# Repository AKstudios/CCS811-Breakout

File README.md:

# CCS811 Breakout
This is a breakout board for the <a href="http://www.ccmoss.com/gas-sensors#CCS811">CCS811</a>(VOC/eCO2) gas sensor by <a href="http://ams.com/eng/Products/Environmental-Sensors/Gas-Sensors/CCS811">AMS</a>. All necessary pins for interfacing with the sensor are broken out. There is no external temperature and relative humidity sensor on the breakout and hence, the AUX pin is left floating. Temperature and relative humidity data from an external sensor can be manually written to ENV_DATA register (0x05) for dynamic compensation. Optionally, you can add 10K-ohm pull-ups on SDA and SCL when using with other devices on the bus.

Note: After reflow, allow 24-48 hours of burn-in time before the sensor starts reporting any good readings.

Arduino library available <a href="https://github.com/AKstudios/CCS811-library">here</a>.

<p align="center"><a href="https://oshpark.com/shared_projects/Z87HMosP"></img></a></p>

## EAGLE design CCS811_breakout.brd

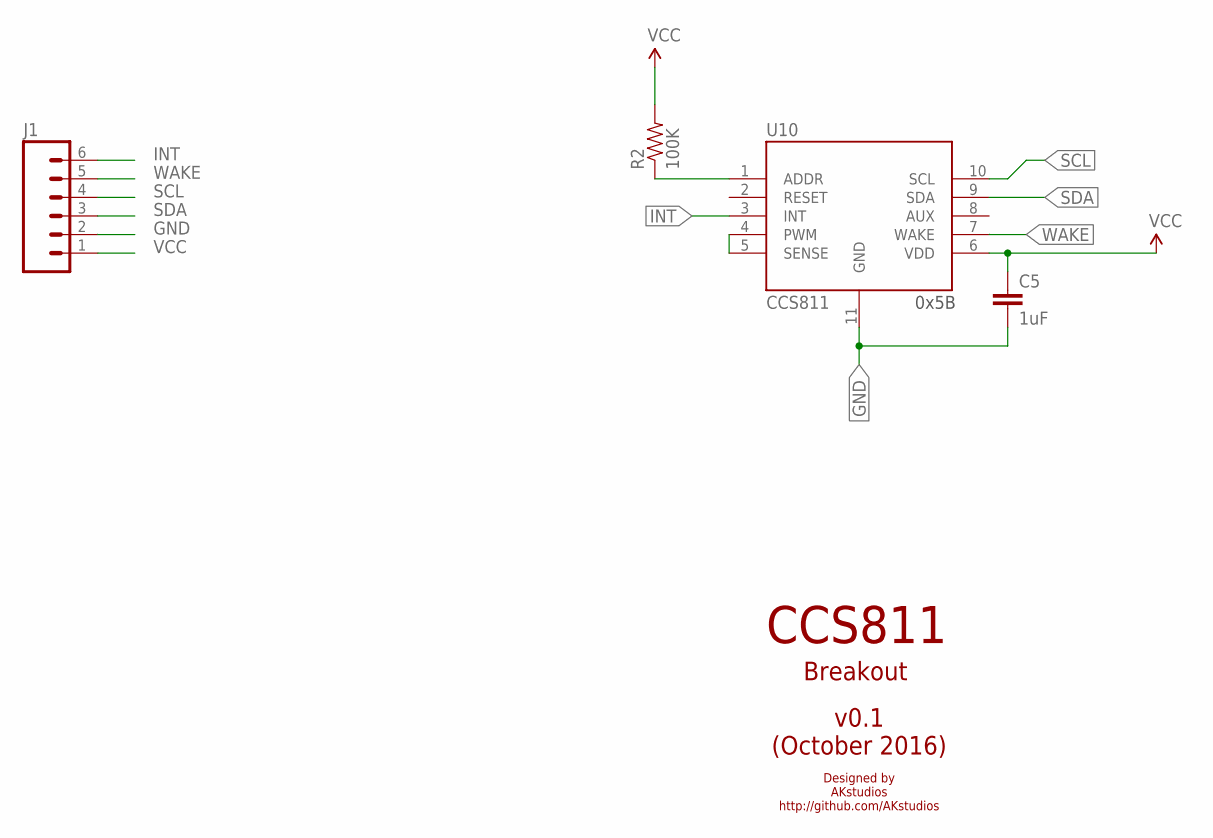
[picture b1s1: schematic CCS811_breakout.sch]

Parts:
C5: 1uF; 0805
J1: M06SILK_FEMALE_PTH; 1X06
R2: 100K; 0805
U10: CCS811; LGA

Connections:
GND: C5.2, J1.2, U10.11 (GND)
INT: J1.6, U10.3 (INT)
unnamed: R2.1, U10.1 (ADDR)
unnamed: U10.4 (PWM), U10.5 (SENSE)
SCL: J1.4, U10.10 (SCL)
SDA: J1.3, U10.9 (SDA)
VCC: C5.1, J1.1, R2.2, U10.6 (VDD)
WAKE: J1.5, U10.7 (WAKE)

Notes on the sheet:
CCS811
Breakout
v0.1 (October 2016)
Designed by AKstudios http://github.com/AKstudios
0x5B

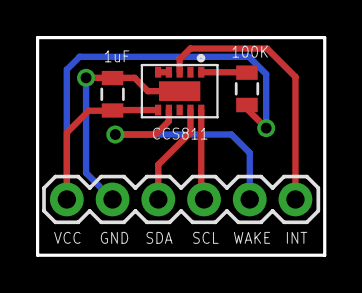
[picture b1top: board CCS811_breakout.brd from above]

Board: 2 copper layers, 16.0 x 12.1 mm, 4 parts (0 on the bottom side), 8 nets.

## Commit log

2016-10-11 :neckbeard: Added .gitattributes & .gitignore files
2016-10-11 Added eagle files
2016-10-11 Updated brd file
2016-10-11 Added 1x4 header
2016-10-11 Updated the board layout
2016-10-11 Updated schematic
2016-10-12 Added PDF of traces and pads
    For manual etching
2016-10-12 Added OSH Park render
2016-10-18 Adjusted GND trace
    Also changed board dimensions; added silkscreen
2016-10-18 Added OSHPark render
2016-10-18 Adjusted board dimensions
2016-10-18 Updated OSH Park render
2016-10-21 Broken essential pins out
    INT and WAKE pins are now broken out
    Updated capacitor to 1uF as recommended by datasheet
2016-10-21 Adjusted traces
2016-10-21 Added library
2016-10-21 Optimized layout; reduced board size
2016-10-21 Updated OSHPark render
2016-10-21 Removed old gerber files
2016-10-25 Changed repo for EAGLE library

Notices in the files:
parts and their libraries:
SparkFun-Passives: Licensing: Creative Commons ShareAlike 4.0 International - https://creativecommons.org/licenses/by-sa/4.0
